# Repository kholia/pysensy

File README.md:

### PySensy

Python "library" for controlling `Sensy IR Cable` + `Mi IR Cable`. This IR
Cable is essentially a USB enabled `IR Universal Remote`.

While we have the IR cable hardware we didn't have the software to use it as
a IR remote control...until now.

ATTENTION: This educational reverse engineering work was carried for enabling
'software interoperability' of Sensy Hardware with Linux (+ other free
systems). Any commercial/pecuniary usage is STRICTLY FORBIDDEN and is at your
own risk!

<br>

### Device Discovery

```
$ dmesg
[14520.215997] usb 1-2: new full-speed USB device number 8 using xhci_hcd
[14520.344268] usb 1-2: New USB device found, idVendor=2717, idProduct=003d, bcdDevice= 1.00
[14520.344276] usb 1-2: New USB device strings: Mfr=1, Product=2, SerialNumber=0
[14520.344281] usb 1-2: Product: Sensy USB Consumer IR Dongle
[14520.344285] usb 1-2: Manufacturer: Sensara Technologies
```

```
$ lsusb
Bus 001 Device 008: ID 2717:003d Xiaomi Inc. Sensy USB Consumer IR Dongle
```

```
$ udevadm control --reload-rules && udevadm trigger
```

Here are the USB interface descriptors present on this device.

```
$ lsusb -vvv
DEVICE ID 2717:003d on Bus 001 Address 009 =================
 bLength                :   0x12 (18 bytes)
 bDescriptorType        :    0x1 Device
 bcdUSB                 :  0x200 USB 2.0
 bDeviceClass           :    0x0 Specified at interface
 bDeviceSubClass        :    0x0
 bDeviceProtocol        :    0x0
 bMaxPacketSize0        :   0x40 (64 bytes)
 idVendor               : 0x2717
 idProduct              : 0x003d
 bcdDevice              :  0x100 Device 1.0
 iManufacturer          :    0x1 Sensara Technologies
 iProduct               :    0x2 Sensy USB Consumer IR Dongle
 iSerialNumber          :    0x0
 bNumConfigurations     :    0x1
  CONFIGURATION 1: 500 mA ==================================
   bLength              :    0x9 (9 bytes)
   bDescriptorType      :    0x2 Configuration
   wTotalLength         :   0x2e (46 bytes)
   bNumInterfaces       :    0x1
   bConfigurationValue  :    0x1
   iConfiguration       :    0x0
   bmAttributes         :   0x80 Bus Powered
   bMaxPower            :   0xfa (500 mA)
    INTERFACE 0: Vendor Specific ===========================
     bLength            :    0x9 (9 bytes)
     bDescriptorType    :    0x4 Interface
     bInterfaceNumber   :    0x0
     bAlternateSetting  :    0x0
     bNumEndpoints      :    0x4
     bInterfaceClass    :   0xff Vendor Specific
     bInterfaceSubClass :   0xff
     bInterfaceProtocol :   0xff
     iInterface         :    0x0
      ENDPOINT 0x81: Interrupt IN ==========================
       bLength          :    0x7 (7 bytes)
       bDescriptorType  :    0x5 Endpoint
       bEndpointAddress :   0x81 IN
       bmAttributes     :    0x3 Interrupt
       wMaxPacketSize   :   0x40 (64 bytes)
       bInterval        :    0x1
      ENDPOINT 0x2: Interrupt OUT ==========================
       bLength          :    0x7 (7 bytes)
       bDescriptorType  :    0x5 Endpoint
       bEndpointAddress :    0x2 OUT
       bmAttributes     :    0x3 Interrupt
       wMaxPacketSize   :   0x40 (64 bytes)
       bInterval        :    0x1
      ENDPOINT 0x83: Bulk IN ===============================
       bLength          :    0x7 (7 bytes)
       bDescriptorType  :    0x5 Endpoint
       bEndpointAddress :   0x83 IN
       bmAttributes     :    0x2 Bulk
       wMaxPacketSize   :   0x40 (64 bytes)
       bInterval        :    0x0
      ENDPOINT 0x4: Bulk OUT ===============================
       bLength          :    0x7 (7 bytes)
       bDescriptorType  :    0x5 Endpoint
       bEndpointAddress :    0x4 OUT
       bmAttributes     :    0x2 Bulk
       wMaxPacketSize   :   0x40 (64 bytes)
       bInterval        :    0x0
```

The devices accepts various command opcodes on its `command_endpoint`. These
opcodes were determined by reversing the `Sensy Remote` Android app.

### Setup

```
pip3 install -r requirements.txt
```

### Work Notes

https://github.com/skylot/jadx was used to reverse engineer the "Sensy Remote"
APK file.

Dynamic tracing notes:

```
$ frida-trace -U -n co.sensara.appsense -j '*!*PulseSequence*/isu'
Started tracing 14 functions. Press Ctrl+C to stop.
           /* TID 0x4c61 */
 71156 ms  PulseSequence.space(3800)
 71160 ms  <= "<instance: co.sensara.sensy.infrared.PulseSequence>"
 71163 ms  PulseSequence.$init()
 71164 ms  PulseSequence.space(9158)
 71166 ms  <= "<instance: co.sensara.sensy.infrared.PulseSequence>"
 71168 ms  PulseSequence.space(12958)
 71170 ms  <= "<instance: co.sensara.sensy.infrared.PulseSequence>"
           /* TID 0x4cc8 */
 71172 ms  Code.getPulseSequence()
 71173 ms  <= "<instance: co.sensara.sensy.infrared.PulseSequence>"
 71178 ms  PulseSequence.flatten("<instance: java.util.List, $className: java.util.ArrayList>")
 71180 ms     | PulseSequence.$init("<instance: co.sensara.sensy.infrared.PulseSequence>")
 71184 ms  <= "<instance: co.sensara.sensy.infrared.PulseSequence>"
```

```
http://irdb.tk/find/ <- Lovely!

For "Samsung TV Menu" keypress (E0E058A7). This TV uses "Protocol NECx2".

Menu -> 00 00 25 00 D0 04 08 D0 08 D0 01 1A 03 4E 01 1A 01 1A 01 1A 5A DE A2 01 11 22 22 21 11 22 22 22 12 11 22 21 21 22 11 13
```

```
$ frida-trace -U -n co.sensara.appsense -j '*!*extract*/isu'
Started tracing 5 functions. Press Ctrl+C to stop.
           /* TID 0x4cc8 */
  5498 ms  PulseSequence.extract()
  5500 ms  <= [171,171,21,60,21,60,21,60,21,21,21,21,21,21,21,21,21,21,21,60,21,60,21,60,21,21,21,21,21,21,21,21,21,21,21,21,21,60,21,21,21,60,21,60,21,21,21,21,21,21,21,60,21,21,21,60,21,21,21,21,21,60,21,60,21,60,21]
C9480000
```

```
$ frida-trace -U -n co.sensara.appsense -j '*!*infrare*/isu'

Started tracing 169 functions. Press Ctrl+C to stop.
           /* TID 0x4c61 */
  4070 ms  IRManager.getInstance()
  4074 ms  <= "<instance: co.sensara.sensy.infrared.IRManager>"
  4076 ms  IRManager.getSelectedOutputDevice()
  4079 ms  <= "<instance: co.sensara.sensy.infrared.ConsumerIRManager, $className: co.sensara.sensy.infrared.IMUStabilizedRemote>"
  4079 ms  IRManager.getInstance()
  4080 ms  <= "<instance: co.sensara.sensy.infrared.IRManager>"
  4106 ms  IRManager.getInstance()
  4106 ms  <= "<instance: co.sensara.sensy.infrared.IRManager>"
  4107 ms  IRManager.getSelectedOutputDevice()
  4107 ms  <= "<instance: co.sensara.sensy.infrared.ConsumerIRManager, $className: co.sensara.sensy.infrared.IMUStabilizedRemote>"
  4109 ms  BurstSequence.add("<instance: co.sensara.sensy.infrared.BurstSequence>") <-- who calls this and with what data?
  4110 ms  PulseSequence.space(3800)
  4114 ms  <= "<instance: co.sensara.sensy.infrared.PulseSequence>"
  4115 ms  IRManager.send(38000, "<instance: co.sensara.sensy.infrared.BurstSequence>", true, 241)
  4115 ms     | PulseSequence.$init()
  4116 ms     | PulseSequence.space(9158)
  4117 ms     | <= "<instance: co.sensara.sensy.infrared.PulseSequence>"
  4119 ms     | BurstSequence.add("<instance: co.sensara.sensy.infrared.IBurst, $className: co.sensara.sensy.infrared.Gap>")
  4120 ms     | BurstSequence.optimize()
  4121 ms     |    | PulseSequence.space(12958)
  4122 ms     |    | <= "<instance: co.sensara.sensy.infrared.PulseSequence>"
  4123 ms     | <= "<instance: co.sensara.sensy.infrared.BurstSequence>"
  4123 ms     | IMUStabilizedRemote.transmit("<instance: co.sensara.sensy.infrared.BurstSequence>")
           /* TID 0x4cc8 */
```

```
$ frida-trace -U -n co.sensara.appsense -j '*!*transmit*/isu'
Started tracing 7 functions. Press Ctrl+C to stop.
           /* TID 0x4c61 */
  9447 ms  IMUStabilizedRemote.transmit("<instance: co.sensara.sensy.infrared.BurstSequence>")
           /* TID 0x4cc8 */
  9455 ms  ConsumerIRManager$AndroidIRManager.transmit(38000, [171,171,21,60,21,60,21,60,21,21,21,21,21,21,21,21,21,21,21,60,21,60,21,60,21,21,21,21,21,21,21,21,21,21,21,21,21,60,21,21,21,60,21,60,21,21,21,21,21,21,21,60,21,21,21,60,21,21,21,21,21,60,21,60,21,60,21])
```

```
$ frida-trace -U -n co.sensara.appsense -j '*NEC*!*encode*/su'  # now reload "SAMSUNG" menu option.
Started tracing 2 functions. Press Ctrl+C to stop.
           /* TID 0x63b6 */
  4827 ms  NEC_SHORT.encode("3772810873", 32)
  4830 ms  <= "<instance: co.sensara.sensy.infrared.PulseSequence>"
  4831 ms  NEC_SHORT.encode("3772803223", 32)
  4832 ms  <= "<instance: co.sensara.sensy.infrared.PulseSequence>"
  4833 ms  NEC_SHORT.encode("3772839943", 32)
  4833 ms  <= "<instance: co.sensara.sensy.infrared.PulseSequence>"
  4834 ms  NEC_SHORT.encode("3772833823", 32)
  4834 ms  <= "<instance: co.sensara.sensy.infrared.PulseSequence>"
  4835 ms  NEC_SHORT.encode("3772794553", 32)
  4835 ms  <= "<instance: co.sensara.sensy.infrared.PulseSequence>"
  4836 ms  NEC_SHORT.encode("3772778233", 32)
  4836 ms  <= "<instance: co.sensara.sensy.infrared.PulseSequence>"
  4837 ms  NEC_SHORT.encode("3772782313", 32)
  4837 ms  <= "<instance: co.sensara.sensy.infrared.PulseSequence>"
  4837 ms  NEC_SHORT.encode("3772819033", 32)
  4837 ms  <= "<instance: co.sensara.sensy.infrared.PulseSequence>"
  4838 ms  NEC_SHORT.encode("3772789198", 32)
  4838 ms  <= "<instance: co.sensara.sensy.infrared.PulseSequence>"
  4838 ms  NEC_SHORT.encode("3772795063", 32)
  4839 ms  <= "<instance: co.sensara.sensy.infrared.PulseSequence>"
  4839 ms  NEC_SHORT.encode("3772793023", 32)
  4839 ms  <= "<instance: co.sensara.sensy.infrared.PulseSequence>"
  4840 ms  NEC_SHORT.encode("3772829743", 32)
  4840 ms  <= "<instance: co.sensara.sensy.infrared.PulseSequence>"
  4840 ms  NEC_SHORT.encode("3772786903", 32)
  4841 ms  <= "<instance: co.sensara.sensy.infrared.PulseSequence>"
  4841 ms  NEC_SHORT.encode("3772837903", 32)
  4841 ms  <= "<instance: co.sensara.sensy.infrared.PulseSequence>"
  4841 ms  NEC_SHORT.encode("3772782313", 32)
  4842 ms  <= "<instance: co.sensara.sensy.infrared.PulseSequence>"
  4842 ms  NEC_SHORT.encode("3772811383", 32)
  4842 ms  <= "<instance: co.sensara.sensy.infrared.PulseSequence>"
  4843 ms  NEC_SHORT.encode("3772790473", 32)
  4843 ms  <= "<instance: co.sensara.sensy.infrared.PulseSequence>"
  4843 ms  NEC_SHORT.encode("3772784863", 32)
  4844 ms  <= "<instance: co.sensara.sensy.infrared.PulseSequence>"
  4844 ms  NEC_SHORT.encode("3772817503", 32)
  4844 ms  <= "<instance: co.sensara.sensy.infrared.PulseSequence>"
  4845 ms  NEC_SHORT.encode("3772801183", 32)
  4845 ms  <= "<instance: co.sensara.sensy.infrared.PulseSequence>"
  4845 ms  NEC_SHORT.encode("3772780783", 32)
  4845 ms  <= "<instance: co.sensara.sensy.infrared.PulseSequence>"
  4846 ms  NEC_SHORT.encode("3772813423", 32)
  4846 ms  <= "<instance: co.sensara.sensy.infrared.PulseSequence>"
  4846 ms  NEC_SHORT.encode("3772797103", 32)
  4847 ms  <= "<instance: co.sensara.sensy.infrared.PulseSequence>"
  4847 ms  NEC_SHORT.encode("3772788943", 32)
  4847 ms  <= "<instance: co.sensara.sensy.infrared.PulseSequence>"
  4847 ms  NEC_SHORT.encode("3772809343", 32)
  4848 ms  <= "<instance: co.sensara.sensy.infrared.PulseSequence>"
  4848 ms  NEC_SHORT.encode("3772821583", 32)
  4848 ms  <= "<instance: co.sensara.sensy.infrared.PulseSequence>"
  4849 ms  NEC_SHORT.encode("3772805263", 32)
  4849 ms  <= "<instance: co.sensara.sensy.infrared.PulseSequence>"
  4849 ms  NEC_SHORT.encode("3772783333", 32)
  4849 ms  <= "<instance: co.sensara.sensy.infrared.PulseSequence>"
  4850 ms  NEC_SHORT.encode("3772799143", 32) <<< Our "Menu" button
  4850 ms  <= "<instance: co.sensara.sensy.infrared.PulseSequence>"
  4850 ms  NEC_SHORT.encode("3772819543", 32)
  4851 ms  <= "<instance: co.sensara.sensy.infrared.PulseSequence>"
  4851 ms  NEC_SHORT.encode("3772778743", 32)
  4851 ms  <= "<instance: co.sensara.sensy.infrared.PulseSequence>"
```

### Demo

Let's emulate this common remote using `Sensy IR Cable`!

```
$ python3 example.py
[!] Device has been reset
[+] Device version is 1
[+] State: Idle
[+] State: Idle
[+] Device configured OK
[+] Started buffering OK
[+] State: Buffering
[+] Ended buffering OK
[+] State: Emitting
[+] State: Idle
```

This program will emulate the `0` key press of this `Car MP3 Remote`.

Note: NEC is a 32-bit code. The presence of trailing zeroes at the end of
"24-bit IR codes" is fine!

### References

- [The evolution of Sensy Infrared Blasters](https://www.linkedin.com/pulse/evolution-sensy-infrared-blasters-bharath-kumar-mohan/)

- http://www.sensyremote.com/

### Next exercise

So far, we have built software for the hardware (i.e. Sensy IR Cable) we had. As
a bonus exercise, we also built the hardware for the software (`Sensy Remote`
APK) we have ;)

The Sensy Home device lets you use your smartphone as a remote if it doesn't
have an IR Blaster. Thanks to four IR Blasters, it provides 360-degree
coverage. The Sensy Home is powered by a pair of AA batteries (included in the
package), which can last a year according to the brand. If your smartphone
already has an IR Blaster, you can download the free Sensy app and begin using
it as a remote right away (this text is borrowed from the internet).

Our alt-hardware mimics the `Sensy BLE Remote` using a ESP32 Dev Module.

The official `Sensy Android App` detects our `Clone BLE IR Blaster HW` just fine ;)

#### Tip

```
n = 0xFD023000  # new code returned, https://github.com/Arduino-IRremote/Arduino-IRremote/issues/789

In [7]: hex(int('{:08b}'.format(n)[::-1], 2))
Out[7]: '0xc40bf'
```

Also,

```
In [6]: hex(int("%s"%bin(0xFD023000)[::-1][:-2], 2))
Out[6]: '0xc40bf'
```

### References

- https://github.com/kholia/Easy-IR-System

- https://github.com/Arduino-IRremote/

- https://github.com/Arduino-IRremote/Arduino-IRremote/issues/789

- https://en.wikipedia.org/wiki/Digital_Millennium_Copyright_Act (`2015 rulemaking`)

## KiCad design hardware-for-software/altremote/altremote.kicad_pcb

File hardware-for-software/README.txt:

Firmware was generated using https://github.com/NordicSemiconductor/pc-nrfutil.

https://github.com/DigitalSecurity/nrf5x-tools/ ;)

...

$ adb logcat | grep `adb shell ps | grep co.sensara.appsense | cut -c10-15`
...
10-20 19:57:23.694 17036 17036 I IRManager: DB_IR: Checking IR Device
10-20 19:57:23.694 17036 17036 D Remote_Test: Checking IR Device
10-20 19:57:23.694 17036 17036 D Remote_Test: Disconnect BLE REMOTE
10-20 19:57:23.695 17036 17036 I BLEScanner: Starting BLE Scan
10-20 19:57:23.695 17036 17036 D BluetoothAdapter: isLeEnabled(): ON
10-20 19:57:23.698  2060  2697 V bt_stack: [VERBOSE1:bta_gattc_act.cc(175)] bta_gattc_register: state:2
10-20 19:57:23.699 17036 23226 D BluetoothLeScanner: onScannerRegistered() - status=0 scannerId=6 mScannerId=0
10-20 19:57:23.713 17036 17036 I SensyHomeFragment: T1: Found devices: 0
10-20 19:57:23.806 17036 17036 I SensyHomeFragment: T1: Found devices: 0
10-20 19:57:23.850 17036 17036 I SensyHomeFragment: T1: Found devices: 0
10-20 19:57:23.892 17036 17036 I SensyHomeFragment: T1: Found devices: 0
10-20 19:57:23.934 17036 17036 I SensyHomeFragment: T1: Found devices: 0
10-20 19:57:23.974 17036 17036 I SensyHomeFragment: T1: Found devices: 0
10-20 19:57:24.009 17036 17036 I SensyHomeFragment: T1: Found devices: 0
10-20 19:57:24.014 17036 17036 I SensyHomeFragment: T1: Found devices: 0
10-20 19:57:24.058 17036 17036 I SensyHomeFragment: T1: Found devices: 0
10-20 19:57:24.101 17036 17036 I SensyHomeFragment: T1: Found devices: 0
10-20 19:57:24.145 17036 17036 I SensyHomeFragment: T1: Found devices: 0
10-20 19:57:24.192 17036 17036 I SensyHomeFragment: T1: Found devices: 0
10-20 19:57:24.717   747  2702 I vendor.qti.bluetooth@1.0-ibs_handler: DeviceSleep: TX Awake, Sending SLEEP_IND
10-20 19:57:24.717   747  2702 D vendor.qti.bluetooth@1.0-ibs_handler: SerialClockVote: vote for UART CLK OFF
10-20 19:57:33.695 17036 17036 I MainActivity: ENABLE BLE STOPPED
10-20 19:57:33.696 17036 17036 D BluetoothAdapter: isLeEnabled(): ON

After `v1` hack:

```
10-20 20:37:23.719 17060 24013 D BluetoothGatt: onClientConnectionState() - status=0 clientIf=6 device=24:6F:28:B1:03:4A
10-20 20:37:23.719 17060 24013 I BLEConnection: Connected device: 24:6F:28:B1:03:4A
10-20 20:37:23.719 17060 24013 I BLEConnection: Refreshing GATT.
10-20 20:37:23.720 17060 24013 D BluetoothGatt: refresh() - device: 24:6F:28:B1:03:4A
10-20 20:37:23.720 17060 24013 D BluetoothGatt: onClientConnectionState() - status=0 clientIf=6 device=24:6F:28:B1:03:4A
10-20 20:37:23.720 17060 24013 I BLEConnection: Connected device: 24:6F:28:B1:03:4A
10-20 20:37:23.721 17060 24013 I BLEConnection: Starting GATT Discovery
10-20 20:37:23.721 17060 24013 D BluetoothGatt: discoverServices() - device: 24:6F:28:B1:03:4A
10-20 20:37:23.731  2060  2697 I bt_stack: [INFO:gatt_main.cc(919)] gatt_data_process op_code = 17, msg_len = 13
10-20 20:37:23.731  2060  2697 V bt_stack: [VERBOSE1:gatt_cl.cc(1100)] gatt_client_handle_server_rsp op_code: 17, len = 13rsp_code: 17
10-20 20:37:23.746  2060  2697 I bt_stack: [INFO:gatt_main.cc(919)] gatt_data_process op_code = 17, msg_len = 21
10-20 20:37:23.746  2060  2697 V bt_stack: [VERBOSE1:gatt_cl.cc(1100)] gatt_client_handle_server_rsp op_code: 17, len = 21rsp_code: 17

10-20 20:37:23.761  2060  2697 I bt_stack: [INFO:gatt_main.cc(919)] gatt_data_process op_code = 17, msg_len = 21
10-20 20:37:23.761  2060  2697 V bt_stack: [VERBOSE1:gatt_cl.cc(1100)] gatt_client_handle_server_rsp op_code: 17, len = 21rsp_code: 17
10-20 20:37:23.836 17060 24013 D BluetoothGatt: onConnectionUpdated() - Device=24:6F:28:B1:03:4A interval=36 latency=0 timeout=500 status=0
10-20 20:37:24.220 17060 17060 I BLEConnection: Starting GATT Discovery
10-20 20:37:24.220 17060 17060 D BluetoothGatt: discoverServices() - device: 24:6F:28:B1:03:4A
10-20 20:37:24.376 17060 24013 D BluetoothGatt: onConnectionUpdated() - Device=24:6F:28:B1:03:4A interval=6 latency=0 timeout=500 status=0
10-20 20:37:24.513 17060 24013 D BluetoothGatt: onSearchComplete() = Device=24:6F:28:B1:03:4A Status=0
10-20 20:37:24.514 17060 24013 I BLEConnection: Discovering Characteristics: 24:6F:28:B1:03:4A
10-20 20:37:24.514 17060 24013 I BLEConnection: Unable to find characteristic and service on device: 24:6F:28:B1:03:4A
10-20 20:37:24.514 17060 24013 I BLEConnection: GATT Discovery Timed out. Retrying connection.
10-20 20:37:24.514 17060 24013 D BluetoothGatt: close()
10-20 20:37:24.514 17060 24013 D BluetoothGatt: unregisterApp() - mClientIf=6
10-20 20:37:24.516 17060 24013 I BLEConnection: Initiating connection.
10-20 20:37:24.516 17060 24013 D BluetoothGatt: connect() - device: 24:6F:28:B1:03:4A, auto: false
10-20 20:37:24.516 17060 24013 D BluetoothGatt: registerApp()
10-20 20:37:24.516 17060 24013 D BluetoothGatt: registerApp() - UUID=cdc9ef0c-fdbe-4a9c-9cc1-611afe1abb7d
10-20 20:37:24.518  2060  2697 V bt_stack: [VERBOSE1:bta_gattc_act.cc(175)] bta_gattc_register: state:2
10-20 20:37:24.519 17060 24013 D BluetoothGatt: onClientRegistered() - status=0 clientIf=6
10-20 20:37:24.522 17060 24013 D BluetoothGatt: onClientConnectionState() - status=0 clientIf=6 device=24:6F:28:B1:03:4A
10-20 20:37:24.522 17060 24013 I BLEConnection: Connected device: 24:6F:28:B1:03:4A
10-20 20:37:24.522 17060 24013 I BLEConnection: Refreshing GATT.
10-20 20:37:24.522 17060 24013 D BluetoothGatt: refresh() - device: 24:6F:28:B1:03:4A
10-20 20:37:24.522 17060 24013 D BluetoothGatt: onClientConnectionState() - status=0 clientIf=6 device=24:6F:28:B1:03:4A
10-20 20:37:24.523 17060 24013 I BLEConnection: Connected device: 24:6F:28:B1:03:4A
10-20 20:37:24.523 17060 24013 I BLEConnection: Starting GATT Discovery
10-20 20:37:24.523 17060 24013 D BluetoothGatt: discoverServices() - device: 24:6F:28:B1:03:4A
```

Logs:

```
$ adb logcat | grep `adb shell ps | grep co.sensara.appsense | cut -c15-18`

10-25 17:34:59.818  2023  2023 I SensyHomeFragment: T1: Found devices: 1
10-25 17:34:59.818  2023  2023 I SensyHomeFragment: T1: Allowing : 24:6F:28:B1:03:4A Sensy Remote
10-25 17:35:00.371  2023  2023 I MainActivity: ENABLE BLE STOPPED
10-25 17:35:00.372  2023  2023 D BluetoothAdapter: isLeEnabled(): ON
10-25 17:35:00.374  2023  2023 I BLEScanner: Connecting to device: 24:6F:28:B1:03:4A
10-25 17:35:00.375  2023  2023 D BluetoothAdapter: isLeEnabled(): ON
10-25 17:35:00.375  2023  2023 D BluetoothLeScanner: could not find callback wrapper
10-25 17:35:00.375  2023  2023 I TVRemoteFragment: ROX Updating TV Remote Overlay
10-25 17:35:00.375  2023  2023 I ACRemoteFragment: ROX Updating AC Remote Fragment
10-25 17:35:00.377  2023  2023 I BLEConnection: Initiating connection.
10-25 17:35:00.377  2023  2023 D BluetoothGatt: connect() - device: 24:6F:28:B1:03:4A, auto: false
10-25 17:35:00.377  2023  2023 D BluetoothGatt: registerApp()
10-25 17:35:00.378  2023  2023 D BluetoothGatt: registerApp() - UUID=863e6088-9080-4439-8fa2-c5cef6c5953a
10-25 17:35:00.379  2023  2023 I RemoteOverlayFragment: ROX Updaing Remote Overlay
10-25 17:35:00.380  2023 15759 D BluetoothGatt: onClientRegistered() - status=0 clientIf=5
10-25 17:35:00.386  2023  2023 I MainActivity: In TV Provider Changed
10-25 17:35:00.387  2023  2023 I RemoteOverlayFragment: ROX Updaing Remote Overlay
10-25 17:35:00.387  2023  2023 I TVRemoteFragment: ROX Updating TV Remote Overlay
10-25 17:35:00.387  2023  2023 I ACRemoteFragment: ROX Updating AC Remote Fragment
10-25 17:35:00.713  2023 15759 D BluetoothGatt: onClientConnectionState() - status=0 clientIf=5 device=24:6F:28:B1:03:4A
10-25 17:35:00.713  2023 15759 I BLEConnection: Connected device: 24:6F:28:B1:03:4A
10-25 17:35:00.713  2023 15759 I BLEConnection: Starting GATT Discovery
10-25 17:35:00.713  2023 15759 D BluetoothGatt: discoverServices() - device: 24:6F:28:B1:03:4A
10-25 17:35:01.243  2023 15759 D BluetoothGatt: onConnectionUpdated() - Device=24:6F:28:B1:03:4A interval=6 latency=0 timeout=500 status=0
10-25 17:35:01.484  2023 15759 D BluetoothGatt: onSearchComplete() = Device=24:6F:28:B1:03:4A Status=0
10-25 17:35:01.485  2023 15759 I BLEConnection: Discovering Characteristics: 24:6F:28:B1:03:4A
10-25 17:35:01.485  2023 15759 I BLEConnection: Unable to find characteristic and service on device: 24:6F:28:B1:03:4A
...

447999 ms  <= "Connected device: 24:6F:28:B1:03:4A"

```
447999 ms  StringBuilder.toString()
447999 ms  <= "discoverServices() - device: 24:6F:28:B1:03:4A"
448023 ms  StringBuilder.toString()
448024 ms  <= "onConnectionUpdated() - Device=24:6F:28:B1:03:4A interval=6 latency=0 timeout=500 status=35"
448114 ms  StringBuilder.toString()
448114 ms  <= "onConnectionUpdated() - Device=24:6F:28:B1:03:4A interval=6 latency=0 timeout=500 status=0"
448325 ms  ParcelUuid.getUuid()
448326 ms  <= "<instance: java.util.UUID>"
448327 ms  StringBuilder.toString()
448327 ms  <= "00002902-0000-1000-8000-00805f9b34fb"
448326 ms  00002902-0000-1000-8000-00805f9b34fb
448328 ms  StringBuilder.toString()
448328 ms  <= "onSearchComplete() = Device=24:6F:28:B1:03:4A Status=0"
448328 ms  StringBuilder.toString()
448329 ms  <= "Discovering Characteristics: 24:6F:28:B1:03:4A"
448329 ms  StringBuilder.toString()
```

```
$ frida-trace -U -n co.sensara.appsense -j '*!*scanF*/su' -j '*!*getUu*/' -j '*StringB*!*toString*/'
```

After `v2`:

```
$ adb logcat | grep `adb shell ps | grep co.sensara.appsense | cut -c15-18`
10-25 18:31:20.222  1659  1782 I ActivityManager: Start proc 2030:co.sensara.appsense/u0a207 for pre-top-activity {co.sensara.appsense/co.sensara.appsense.SplashActivity}
10-25 19:08:56.625  2030  2030 I RemoteManager: Restoring remotes from user account
10-25 19:08:56.625  2030  2030 I RemoteManager: Account.TVProvider value: null
10-25 19:08:56.626  2030  2030 I RemoteManager: DB0: selectedAC: null and Application.acSubremoteID = null
10-25 19:08:56.627  2030  2030 I BLEConnection: New Persist state: true
10-25 19:08:56.627  2030  2030 I IRManager: DB_IR: Checking IR Device
10-25 19:08:56.627  2030  2030 D Remote_Test: Checking IR Device
10-25 19:08:56.627  2030  2030 D Remote_Test: BLE REMOTE Usable true
10-25 19:08:56.627  2030  2030 I Application: Firing onActivityShown
10-25 19:08:56.633  2030  2030 I Account : Login ID: 62895523
10-25 19:08:56.638  2030  2030 I MainActivity: In TV Provider Changed
10-25 19:08:56.638  2030  2030 I RemoteOverlayFragment: ROX Updaing Remote Overlay
10-25 19:08:56.638  2030  2030 I TVRemoteFragment: ROX Updating TV Remote Overlay
10-25 19:08:56.638  2030  2030 I ACRemoteFragment: ROX Updating AC Remote Fragment
10-25 19:08:56.643  2030 20387 I IRManager: DB_IR: Checking IR Device
10-25 19:08:56.643  2030 20387 D Remote_Test: Checking IR Device
10-25 19:08:56.643  2030 20387 D Remote_Test: BLE REMOTE Usable true
10-25 19:08:56.643  2030 20387 I IRManager: Wifi Is Enabled. Starting Scan
10-25 19:08:56.643  2030 20387 I WifiScanner: WiFi: In startScan with forceScan as: false
10-25 19:08:56.644  2030 20387 I WifiScanner: WiFi: Setting isScanning to True
10-25 19:08:56.644  2030 20387 I WifiScanner: WiFi: Scanning for 10s
```

Nothing extra was needed to make `Remote_Test: BLE REMOTE Usable true`.

```
10-25 19:22:37.942  2030  2030 D Remote_Test: BLE REMOTE Usable true
10-25 19:22:37.943  2030  2030 I TVRemoteFragment: ROX Updating TV Remote Overlay
10-25 19:22:37.943  2030  2030 I ACRemoteFragment: ROX Updating AC Remote Fragment
10-25 19:22:37.946  2030  2030 I RemoteOverlayFragment: ROX Updaing Remote Overlay
10-25 19:22:37.956  2030  2030 I MainActivity: In TV Provider Changed
10-25 19:22:37.956  2030  2030 I RemoteOverlayFragment: ROX Updaing Remote Overlay
10-25 19:22:37.957  2030  2030 I TVRemoteFragment: ROX Updating TV Remote Overlay
10-25 19:22:37.957  2030  2030 I ACRemoteFragment: ROX Updating AC Remote Fragment
10-25 19:22:37.963  2030  2030 I BLEConnection: Reading supported Protocols
10-25 19:22:37.982  2030 19228 I BLEConnection: Supported Custom Protocol: 1214606444
10-25 19:22:37.982  2030 19228 I BLEConnection: Supported Custom Protocol: 1864390511
10-25 19:22:37.982  2030 19228 I BLEConnection: Supported Custom Protocol: 1919706144
10-25 19:22:37.982  2030 19228 I BLEConnection: Supported Custom Protocol: 1935767923
10-25 19:22:37.982  2030 19228 I BLEConnection: Supported Custom Protocol: 542008681
10-25 19:22:37.983  2030 19228 W BluetoothGatt: Unhandled exception in callback
10-25 19:22:37.983  2030 19228 W BluetoothGatt: java.nio.BufferUnderflowException
10-25 19:22:37.983  2030 19228 W BluetoothGatt: 	at java.nio.Buffer.nextGetIndex(Buffer.java:521)
10-25 19:22:37.983  2030 19228 W BluetoothGatt: 	at java.nio.HeapByteBuffer.getInt(HeapByteBuffer.java:319)
10-25 19:22:37.983  2030 19228 W BluetoothGatt: 	at co.sensara.sensy.infrared.bluetooth.BLEConnection.parseSupportedProtocols(BLEConnection.java:817)
10-25 19:22:37.983  2030 19228 W BluetoothGatt: 	at co.sensara.sensy.infrared.bluetooth.BLEConnection.access$1000(BLEConnection.java:40)
10-25 19:22:37.983  2030 19228 W BluetoothGatt: 	at co.sensara.sensy.infrared.bluetooth.BLEConnection$SupportedProtocolReadOperation.onCharacteristicRead(BLEConnection.java:970)
10-25 19:22:37.983  2030 19228 W BluetoothGatt: 	at co.sensara.sensy.infrared.bluetooth.BLEConnection.onCharacteristicRead(BLEConnection.java:769)
10-25 19:22:37.983  2030 19228 W BluetoothGatt: 	at android.bluetooth.BluetoothGatt$1$6.run(BluetoothGatt.java:394)
10-25 19:22:37.983  2030 19228 W BluetoothGatt: 	at android.bluetooth.BluetoothGatt.runOrQueueCallback(BluetoothGatt.java:780)
10-25 19:22:37.983  2030 19228 W BluetoothGatt: 	at android.bluetooth.BluetoothGatt.access$200(BluetoothGatt.java:41)
10-25 19:22:37.983  2030 19228 W BluetoothGatt: 	at android.bluetooth.BluetoothGatt$1.onCharacteristicRead(BluetoothGatt.java:388)
10-25 19:22:37.983  2030 19228 W BluetoothGatt: 	at android.bluetooth.IBluetoothGattCallback$Stub.onTransact(IBluetoothGattCallback.java:246)
10-25 19:22:37.983  2030 19228 W BluetoothGatt: 	at android.os.Binder.execTransactInternal(Binder.java:1021)
10-25 19:22:37.983  2030 19228 W BluetoothGatt: 	at android.os.Binder.execTransact(Binder.java:994)
10-25 19:22:38.038  2030 19228 D BluetoothGatt: onConnectionUpdated() - Device=24:6F:28:B1:03:4A interval=36 latency=0 timeout=500 status=0
```

We need to implement this part (i.e. "supported protocols") now.

After `v3`: Add `Samsung TV` and press a key on the on-screen remote.

```
10-25 19:51:17.765  2030  2030 I RemoteControl: Sequencer: 52Will emit: key: 6 32 e0e058a7; device: e0e00000
10-25 19:51:17.765  2030  2030 I RemoteControl: Final sleep: 241; Gap: 400; Used: 159
10-25 19:51:17.765  2030  2030 I BLEConnection: Writing Characteristic: 24:6F:28:B1:03:4A
10-25 19:51:17.767  2030  2030 I Analytics: AX2 sendEvent 1
10-25 19:51:17.767  2030  2030 I Analytics: AX2 sendEvent 1
10-25 19:51:17.841  2030  2030 I BLEConnection: Writing Characteristic: 24:6F:28:B1:03:4A
10-25 19:51:24.303  2030  2030 I WifiScanner: WiFi: Inside stopScan
10-25 19:51:24.303  2030  2030 I WifiScanner: WiFi: Setting isScanning to False
10-25 19:51:24.303  2030  2030 I WifiScanner: WiFi: Stopped Scan. Here are the devices found:
10-25 19:51:24.303  2030  2030 I WifiScanner: WiFi: Sending it to Sensy Home Fragment.. I guess. Posting Event
10-25 19:51:24.303  2030  2030 I MainActivity: WiFi Devices Found Event Triggered
10-25 19:51:24.305  2030 19200 I WifiScanner: WiFi: Stopped Wifi Discovery
10-25 19:51:48.098  2030  2030 I Application: Firing onActivityHidden
10-25 19:52:04.321  2030  2030 I BLEConnection: New Persist state: false
10-25 19:52:04.322  2030  2030 I BLEConnection: Fast Restart.
10-25 19:52:04.322  2030  2030 I BLEConnection: Writing Characteristic: 24:6F:28:B1:03:4A
10-25 19:52:04.323  2030  2030 I IRManager: DB_IR: Checking IR Device
10-25 19:52:04.323  2030  2030 D Remote_Test: Checking IR Device
10-25 19:52:04.323  2030  2030 D Remote_Test: BLE REMOTE Usable true
10-25 19:52:04.326  2030  2030 I RemoteManager: Changing TV Configuration - Provider: null, TV Manufacturer: 3, Selected Remote: null, Referrer: RemoteManager
10-25 19:52:04.326  2030  2030 I RemoteManager: Operator Selection: Change TV Configuration called with provider: Null
10-25 19:52:04.326  2030  2030 I RemoteManager: Operator Selection: Trying to getTelevision with Provider: Null
10-25 19:52:04.326  2030  2030 I Backend : Operator Selection: Building Result with provider: null
10-25 19:52:04.425  2030  2030 I MainActivity: In TV Provider Changed
10-25 19:52:04.425  2030  2030 I RemoteOverlayFragment: ROX Updaing Remote Overlay
10-25 19:52:04.427  2030  2030 I TVRemoteFragment: ROX Updating TV Remote Overlay
10-25 19:52:04.427  2030  2030 I ACRemoteFragment: ROX Updating AC Remote Fragment
10-25 19:52:04.429  2030  2030 D BluetoothGatt: cancelOpen() - device: 24:6F:28:B1:03:4A
10-25 19:52:04.431  2030 19100 D BluetoothGatt: onClientConnectionState() - status=0 clientIf=10 device=24:6F:28:B1:03:4A
10-25 19:52:04.431  2030 19100 I BLEConnection: Finished output on: 24:6F:28:B1:03:4A
10-25 19:52:04.431  2030 19100 D BluetoothGatt: close()
10-25 19:52:04.431  2030 19100 D BluetoothGatt: unregisterApp() - mClientIf=10
10-25 19:52:04.431  2030  2030 I RemoteUtils: Remote: Current remote ID is null
10-25 19:52:04.435  2030 19147 I LCNStore: Using Offline remote control data for remotes: 52, 92
10-25 19:52:04.443  2030  2030 I MainActivity: In TV Provider Changed
10-25 19:52:04.443  2030  2030 I RemoteOverlayFragment: ROX Updaing Remote Overlay
10-25 19:52:04.445  2030  2030 I TVRemoteFragment: ROX Updating TV Remote Overlay
```

```
$ frida-trace -U -n co.sensara.appsense -j '*!*writeCha*/'
 60899 ms  BluetoothGatt.writeCharacteristic("<instance: android.bluetooth.BluetoothGattCharacteristic>")
 60900 ms     | IBluetoothGatt$Stub$Proxy.writeCharacteristic(9, "24:6F:28:B1:03:4A", 61, 2, 0, [6,32,0,0,0,0,-32,-32,88,-89,0,0,0,0,0,0,0,0,0,0])
 60901 ms  <= true
 60969 ms  BluetoothGatt.writeCharacteristic("<instance: android.bluetooth.BluetoothGattCharacteristic>")
 60969 ms     | IBluetoothGatt$Stub$Proxy.writeCharacteristic(9, "24:6F:28:B1:03:4A", 61, 2, 0, [-1,0,0,1,85,0,0,0,0,0,0,0,0,0,0,0,0,0,0,0])
 60971 ms  <= true
```

```
Started tracing 80 functions. Press Ctrl+C to stop.
           /* TID 0x3ddd */
  4073 ms  Sequencer.parseCode("0xe0e08679")
  4073 ms  <= "3772810873"
  4074 ms  NEC_SHORT.encode("3772810873", 32)
  4075 ms  <= "<instance: co.sensara.sensy.infrared.PulseSequence>"
  4075 ms  Sequencer.parseCode("0xe0e06897")
  4075 ms  <= "3772803223"
  4075 ms  NEC_SHORT.encode("3772803223", 32)
  4075 ms  <= "<instance: co.sensara.sensy.infrared.PulseSequence>"
  4076 ms  Sequencer.parseCode("0xe0e0f807")
  4076 ms  <= "3772839943"
  4076 ms  NEC_SHORT.encode("3772839943", 32)
  4076 ms  <= "<instance: co.sensara.sensy.infrared.PulseSequence>"
  4076 ms  Sequencer.parseCode("0xe0e0e01f")
  4076 ms  <= "3772833823"
  4076 ms  NEC_SHORT.encode("3772833823", 32)
  4076 ms  <= "<instance: co.sensara.sensy.infrared.PulseSequence>"
  4076 ms  Sequencer.parseCode("0xe0e046b9")
  4076 ms  <= "3772794553"
  4076 ms  NEC_SHORT.encode("3772794553", 32)
  4077 ms  <= "<instance: co.sensara.sensy.infrared.PulseSequence>"
  4077 ms  Sequencer.parseCode("0xe0e006f9")
  4077 ms  <= "3772778233"
  4077 ms  NEC_SHORT.encode("3772778233", 32)
  4077 ms  <= "<instance: co.sensara.sensy.infrared.PulseSequence>"
  4077 ms  Sequencer.parseCode("0xe0e016e9")
  4077 ms  <= "3772782313"
  4077 ms  NEC_SHORT.encode("3772782313", 32)
  4077 ms  <= "<instance: co.sensara.sensy.infrared.PulseSequence>"
  4077 ms  Sequencer.parseCode("0xe0e0a659")
  4077 ms  <= "3772819033"
  4078 ms  NEC_SHORT.encode("3772819033", 32)
  4078 ms  <= "<instance: co.sensara.sensy.infrared.PulseSequence>"
  4078 ms  Sequencer.parseCode("0xe0e031ce")
  4078 ms  <= "3772789198"
  4078 ms  NEC_SHORT.encode("3772789198", 32)
  4078 ms  <= "<instance: co.sensara.sensy.infrared.PulseSequence>"
  4078 ms  Sequencer.parseCode("0xe0e048b7")
  4078 ms  <= "3772795063"
  4078 ms  NEC_SHORT.encode("3772795063", 32)
  4079 ms  <= "<instance: co.sensara.sensy.infrared.PulseSequence>"
  4079 ms  Sequencer.parseCode("0xe0e040bf")
  4079 ms  <= "3772793023"
  4079 ms  NEC_SHORT.encode("3772793023", 32)
  4079 ms  <= "<instance: co.sensara.sensy.infrared.PulseSequence>"
  4079 ms  Sequencer.parseCode("0xe0e0d02f")
  4079 ms  <= "3772829743"
  4079 ms  NEC_SHORT.encode("3772829743", 32)
  4079 ms  <= "<instance: co.sensara.sensy.infrared.PulseSequence>"
  4079 ms  Sequencer.parseCode("0xe0e028d7")
  4079 ms  <= "3772786903"
  4079 ms  NEC_SHORT.encode("3772786903", 32)
  4080 ms  <= "<instance: co.sensara.sensy.infrared.PulseSequence>"
  4080 ms  Sequencer.parseCode("0xe0e0f00f")
  4080 ms  <= "3772837903"
  4080 ms  NEC_SHORT.encode("3772837903", 32)
  4080 ms  <= "<instance: co.sensara.sensy.infrared.PulseSequence>"
  4080 ms  Sequencer.parseCode("0xe0e016e9")
  4080 ms  <= "3772782313"
  4080 ms  NEC_SHORT.encode("3772782313", 32)
  4080 ms  <= "<instance: co.sensara.sensy.infrared.PulseSequence>"
  4080 ms  Sequencer.parseCode("0xe0e08877")
  4080 ms  <= "3772811383"
  4080 ms  NEC_SHORT.encode("3772811383", 32)
  4081 ms  <= "<instance: co.sensara.sensy.infrared.PulseSequence>"
  4081 ms  Sequencer.parseCode("0xe0e036c9")
  4081 ms  <= "3772790473"
  4081 ms  NEC_SHORT.encode("3772790473", 32)
  4081 ms  <= "<instance: co.sensara.sensy.infrared.PulseSequence>"
  4081 ms  Sequencer.parseCode("0xe0e020df")
  4081 ms  <= "3772784863"
  4081 ms  NEC_SHORT.encode("3772784863", 32)
  4081 ms  <= "<instance: co.sensara.sensy.infrared.PulseSequence>"
  4081 ms  Sequencer.parseCode("0xe0e0a05f")
  4082 ms  <= "3772817503"
  4082 ms  NEC_SHORT.encode("3772817503", 32)
  4082 ms  <= "<instance: co.sensara.sensy.infrared.PulseSequence>"
  4082 ms  Sequencer.parseCode("0xe0e0609f")
  4082 ms  <= "3772801183"
  4082 ms  NEC_SHORT.encode("3772801183", 32)
  4082 ms  <= "<instance: co.sensara.sensy.infrared.PulseSequence>"
  4082 ms  Sequencer.parseCode("0xe0e010ef")
  4082 ms  <= "3772780783"
  4083 ms  NEC_SHORT.encode("3772780783", 32)
  4083 ms  <= "<instance: co.sensara.sensy.infrared.PulseSequence>"
  4083 ms  Sequencer.parseCode("0xe0e0906f")
  4083 ms  <= "3772813423"
  4083 ms  NEC_SHORT.encode("3772813423", 32)
  4083 ms  <= "<instance: co.sensara.sensy.infrared.PulseSequence>"
  4083 ms  Sequencer.parseCode("0xe0e050af")
  4083 ms  <= "3772797103"
  4083 ms  NEC_SHORT.encode("3772797103", 32)
  4084 ms  <= "<instance: co.sensara.sensy.infrared.PulseSequence>"
  4084 ms  Sequencer.parseCode("0xe0e030cf")
  4084 ms  <= "3772788943"
  4084 ms  NEC_SHORT.encode("3772788943", 32)
  4084 ms  <= "<instance: co.sensara.sensy.infrared.PulseSequence>"
  4084 ms  Sequencer.parseCode("0xe0e0807f")
  4084 ms  <= "3772809343"
  4084 ms  NEC_SHORT.encode("3772809343", 32)
  4084 ms  <= "<instance: co.sensara.sensy.infrared.PulseSequence>"
  4085 ms  Sequencer.parseCode("0xe0e0b04f")
  4085 ms  <= "3772821583"
  4085 ms  NEC_SHORT.encode("3772821583", 32)
  4085 ms  <= "<instance: co.sensara.sensy.infrared.PulseSequence>"
  4085 ms  Sequencer.parseCode("0xe0e0708f")
  4085 ms  <= "3772805263"
  4085 ms  NEC_SHORT.encode("3772805263", 32)
  4085 ms  <= "<instance: co.sensara.sensy.infrared.PulseSequence>"
  4085 ms  Sequencer.parseCode("0xe0e01ae5")
  4086 ms  <= "3772783333"
  4086 ms  NEC_SHORT.encode("3772783333", 32)
  4086 ms  <= "<instance: co.sensara.sensy.infrared.PulseSequence>"
  4086 ms  Sequencer.parseCode("0xe0e058a7")
  4086 ms  <= "3772799143"
  4086 ms  NEC_SHORT.encode("3772799143", 32)
  4086 ms  <= "<instance: co.sensara.sensy.infrared.PulseSequence>"
  4086 ms  Sequencer.parseCode("0xe0e0a857")
  4086 ms  <= "3772819543"
  4086 ms  NEC_SHORT.encode("3772819543", 32)
  4087 ms  <= "<instance: co.sensara.sensy.infrared.PulseSequence>"
  4087 ms  Sequencer.parseCode("0xe0e008f7")
  4087 ms  <= "3772778743"
  4087 ms  NEC_SHORT.encode("3772778743", 32)
  4087 ms  <= "<instance: co.sensara.sensy.infrared.PulseSequence>"
  4087 ms  Sequencer.parseCode("0x800")
  4087 ms  <= "2048"
  4087 ms  Sequencer.parseCode("0x1fee")
  4087 ms  <= "8174"
  4088 ms  Sequencer.parseCode("0x1fea")
  4088 ms  <= "8170"
  4088 ms  Sequencer.parseCode("0x1fef")
  4088 ms  <= "8175"
  4088 ms  Sequencer.parseCode("0x0ff3")
  4088 ms  <= "4083"
  4088 ms  Sequencer.parseCode("0x1fea")
  4088 ms  <= "8170"
  4088 ms  Sequencer.parseCode("0x0ff2")
  4088 ms  <= "4082"
  4088 ms  Sequencer.parseCode("0x0fe1")
  4088 ms  <= "4065"
  4088 ms  Sequencer.parseCode("0x1fe9")
  4088 ms  <= "8169"
  4089 ms  Sequencer.parseCode("0x0fc7")
  4089 ms  <= "4039"
  4089 ms  Sequencer.parseCode("0x1fce")
  4089 ms  <= "8142"
  4089 ms  Sequencer.parseCode("0x1fe9")
  4089 ms  <= "8169"
  4089 ms  Sequencer.parseCode("0x1fef")
  4089 ms  <= "8175"
  4089 ms  Sequencer.parseCode("0x1fee")
  4089 ms  <= "8174"
  4089 ms  Sequencer.parseCode("0x0fe1")
  4089 ms  <= "4065"
  4089 ms  Sequencer.parseCode("0x1fce")
  4089 ms  <= "8142"
```

```
           /* TID 0x3ddf */
  9332 ms  RemoteControl.sendCode("MENU", "tv")
  9356 ms     | RemoteControl.sendCode("MENU", true)
  9356 ms     |    | InterleavedRemote.dispatchCode("MENU", true)
  9357 ms     |    |    | InterleavedRemote$InterleavedRemoteSet.sendCode("MENU", true)
  9357 ms     |    |    |    | Sequencer$SimpleSequencer.getBurstSequence("MENU")
  9358 ms     |    |    |    | <= "<instance: co.sensara.sensy.infrared.BurstSequence>"
  9358 ms     |    |    |    | BurstSequence.getBursts()
  9359 ms     |    |    |    | <= "<instance: java.util.List, $className: java.util.Collections$UnmodifiableRandomAccessList>"
  9359 ms     |    |    |    | BurstSequence.getBursts()
  9360 ms     |    |    |    | <= "<instance: java.util.List, $className: java.util.Collections$UnmodifiableRandomAccessList>"
  9360 ms     |    |    | InterleavedRemote$InterleavedRemoteSet.sendCode("MENU", false)
  9360 ms     |    |    |    | Sequencer$ToggleSequencer.getBurstSequence("MENU")
  9360 ms     |    |    |    | <= null
  9361 ms     | BluetoothGatt.writeCharacteristic("<instance: android.bluetooth.BluetoothGattCharacteristic>")
  9362 ms     |    | IBluetoothGatt$Stub$Proxy.writeCharacteristic(5, "24:6F:28:B1:03:4A", 61, 2, 0, [6,32,0,0,0,0,-32,-32,88,-89,0,0,0,0,0,0,0,0,0,0])
```

062000000000e0e058a700000000000000000000

06 -> NEC protocol

0x20 -> 32 -> length of the code (4 bytes -> 32 bits)

-32,-32,88,-89 is actually -> e0e058a7 -> neat!

Next steps ->

-> Build a safe IR led circuit for ESP32 (3.3v pins).

Easiest -> https://github.com/crankyoldgit/IRremoteESP8266/blob/master/examples/IRsendDemo/IRsendDemo.ino

https://www.analysir.com/blog/2015/09/01/simple-infrared-pwm-on-arduino-part-3-hex-ir-signals/

https://www.analysir.com/blog/2015/05/12/simple-infrared-pwm-on-arduino/

https://github.com/Darryl-Scott/ESP32-RMT-Library-IR-code-RAW

https://github.com/crankyoldgit/IRremoteESP8266

...

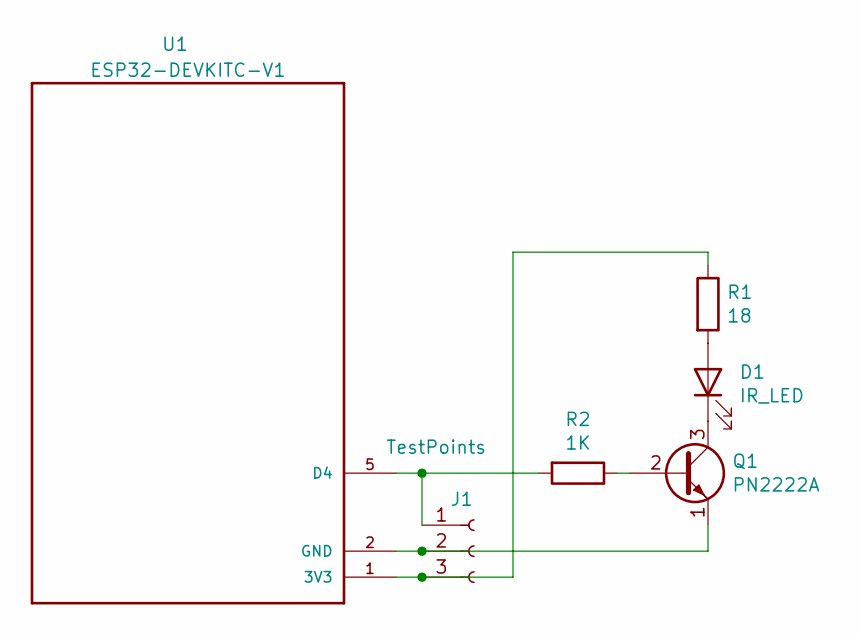
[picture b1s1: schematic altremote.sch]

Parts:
D1: IR_LED; LED_D5.0mm_Horizontal_O1.27mm_Z3.0mm_IRGrey
J1: TestPoints; PinHeader_1x03_P2.54mm_Vertical
Q1: PN2222A; TO-92_Inline
R1: 18; R_Axial_DIN0207_L6.3mm_D2.5mm_P7.62mm_Horizontal
R2: 1K; R_Axial_DIN0207_L6.3mm_D2.5mm_P7.62mm_Horizontal
U1: ESP32-DEVKITC-V1; esp32_devkit_v1_doit_modded

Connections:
unnamed: D1.1 (K), Q1.3 (C)
unnamed: D1.2 (A), R1.2
unnamed: J1.1, R2.2, U1.5 (D4)
unnamed: J1.2, Q1.1 (E), U1.2 (GND)
unnamed: J1.3, R1.1, U1.1 (3V3)
unnamed: Q1.2 (B), R2.1

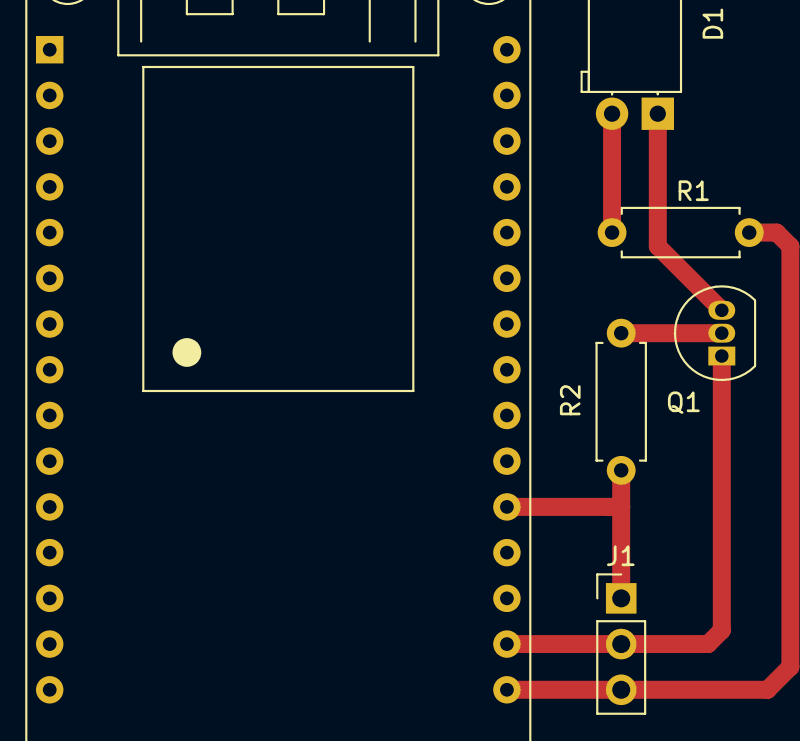
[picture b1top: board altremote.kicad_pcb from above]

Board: 2 copper layers, 6 parts (0 on the bottom side), 6 nets.

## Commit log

2021-06-08 Educational PoC
